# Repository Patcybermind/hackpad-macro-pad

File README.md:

# Pat's macropad
this was made for [highway](https://highway.hackclub.com) 
like some of the other projects on my github

## Features
- 8 keys
- oled display
- multiple modes / key presets

## PCB
Here are pictures of my pcb:

| **Schematic** | **PCB** |
|---------------|---------|
|||

[x] I ran DRC and there are 0 errors

## CAD

top and bottom are joined with m3 screws and heat inserts

## Firmware

The display tells you what mode you are in and in can be cycled with one of the keys

## BOM
- 1 SEEEDUINO XIAO RP2040
- 8x hackpad switches
- 8x hackpad keycaps
- 1x hackpad oled display
- 2x hackpad neopixels
- 4x M3x16mm screws
- 4x M3x5mx4mm heatset inserts

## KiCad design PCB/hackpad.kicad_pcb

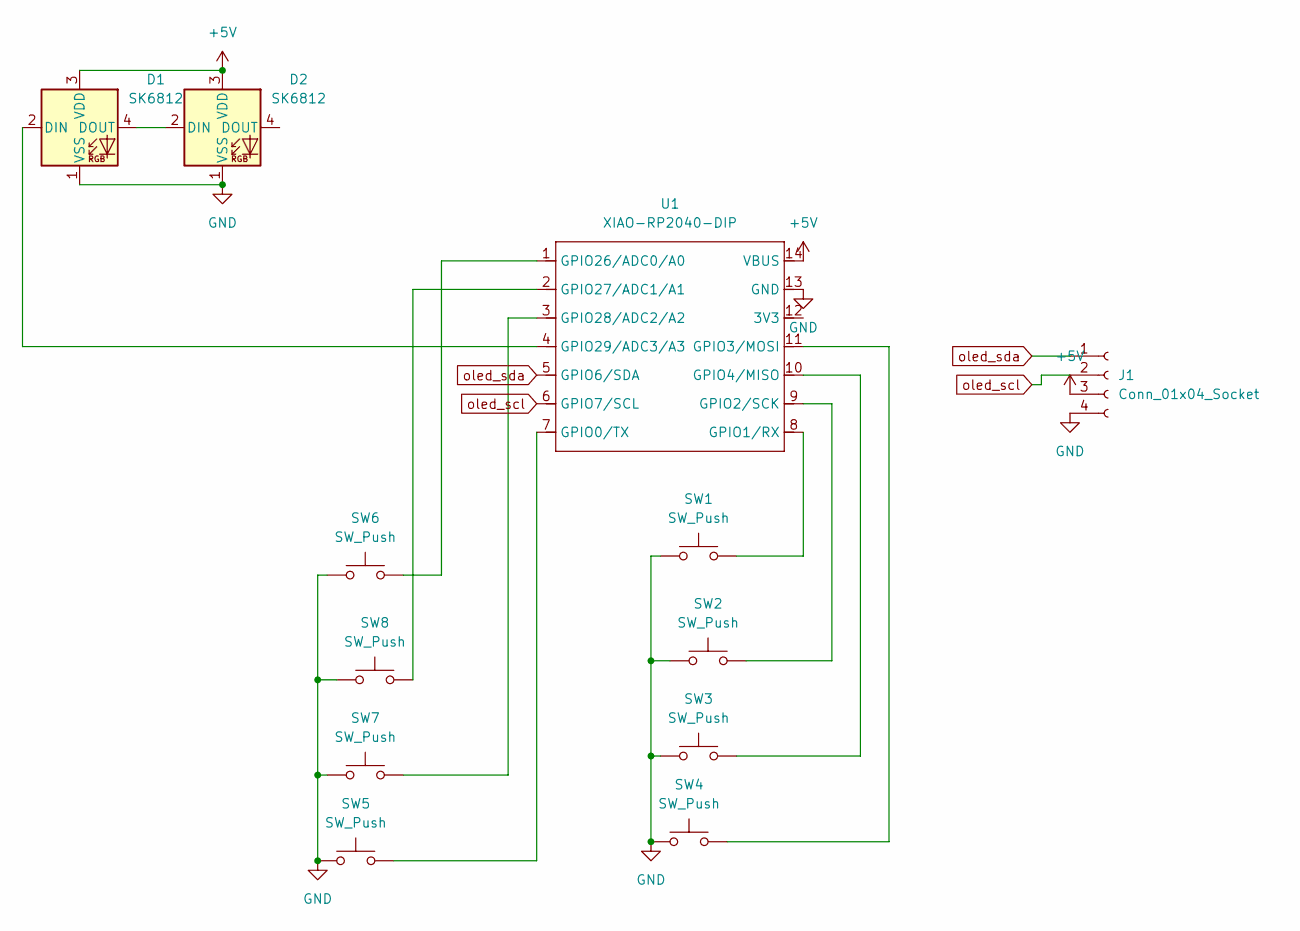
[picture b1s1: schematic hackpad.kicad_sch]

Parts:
D1, D2: SK6812; LED_SK6812_PLCC4_5.0x5.0mm_P3.2mm
J1: Conn_01x04_Socket; PinHeader_1x04_P2.54mm_Vertical
SW1, SW2, SW3, SW4, SW5, SW6, SW7, SW8: SW_Push; SW_Cherry_MX_1.00u_PCB
U1: XIAO-RP2040-DIP

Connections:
+5V: D1.3 (VDD), D2.3 (VDD), J1.3, U1.14 (VBUS)
GND: D1.1 (VSS), D2.1 (VSS), J1.4, SW1.1, SW2.1, SW3.1, SW4.1, SW5.1, SW6.1, SW7.1, SW8.1, U1.13 (GND)
unnamed: D1.2 (DIN), U1.4 (GPIO29/ADC3/A3)
unnamed: D1.4 (DOUT), D2.2 (DIN)
unnamed: SW5.2, U1.7 (GPIO0/TX)
unnamed: SW1.2, U1.8 (GPIO1/RX)
unnamed: SW2.2, U1.9 (GPIO2/SCK)
unnamed: SW4.2, U1.11 (GPIO3/MOSI)
unnamed: SW3.2, U1.10 (GPIO4/MISO)
unnamed: SW6.2, U1.1 (GPIO26/ADC0/A0)
unnamed: SW8.2, U1.2 (GPIO27/ADC1/A1)
unnamed: SW7.2, U1.3 (GPIO28/ADC2/A2)
oled_scl: J1.2, U1.6 (GPIO7/SCL)
oled_sda: J1.1, U1.5 (GPIO6/SDA)

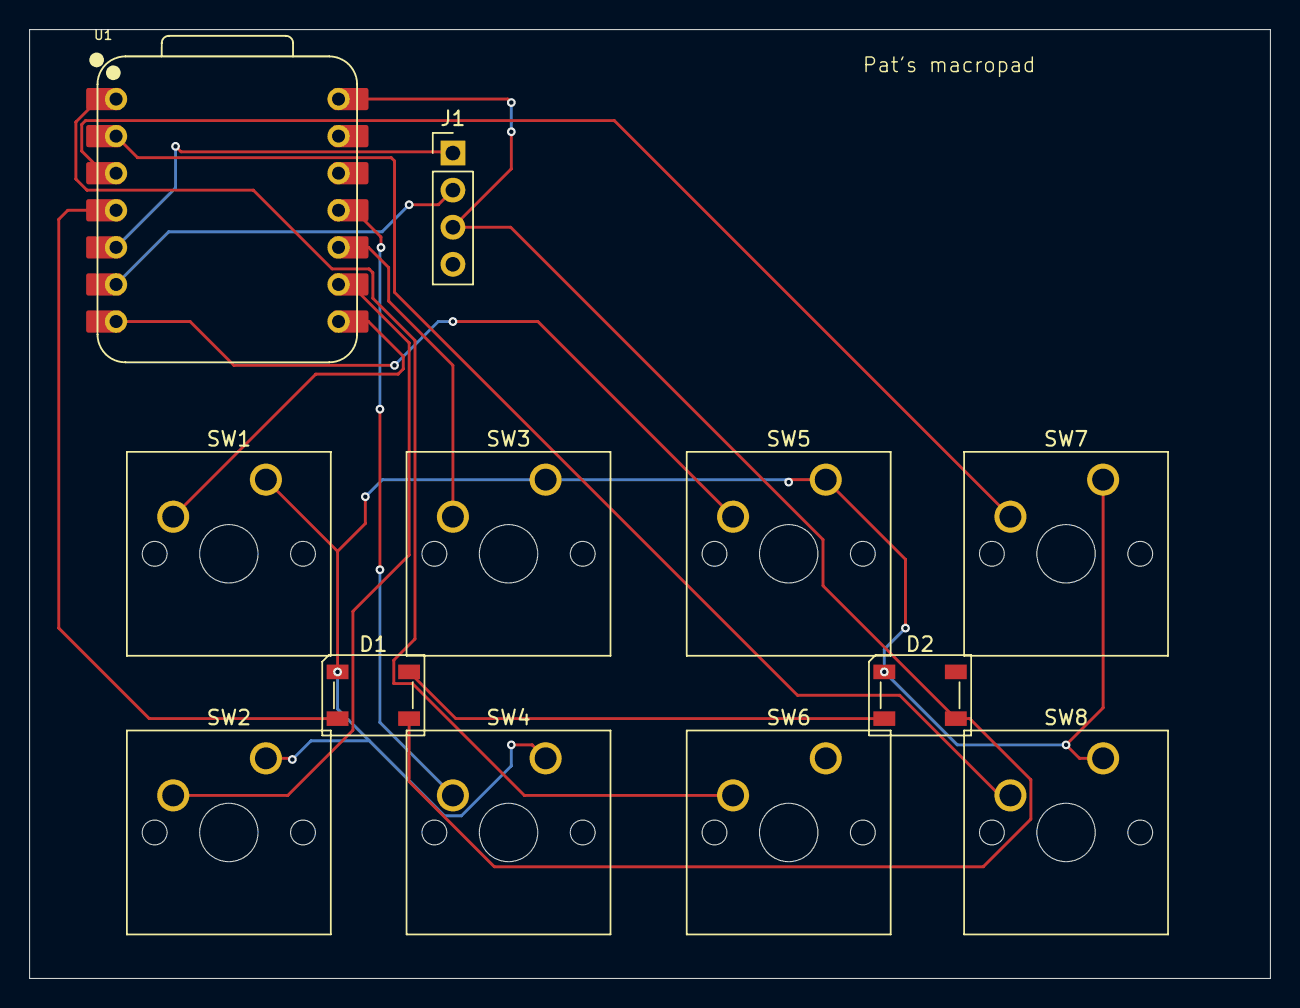
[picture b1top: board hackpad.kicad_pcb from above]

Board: 2 copper layers, 85.0 x 65.0 mm, 12 parts (0 on the bottom side), 14 nets.

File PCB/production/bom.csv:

Designator,Footprint,Quantity,Value,LCSC Part #
"D1, D2",LED_SK6812_PLCC4_5.0x5.0mm_P3.2mm,2,SK6812,
J1,PinHeader_1x04_P2.54mm_Vertical,1,Conn_01x04_Socket,
"SW1, SW2, SW3, SW4, SW5, SW6, SW7, SW8",SW_Cherry_MX_1.00u_PCB,8,SW_Push,
U1,XIAO-RP2040-DIP,1,XIAO-RP2040-DIP,

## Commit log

2025-06-27 added all kicad files
2025-06-29 done
2025-07-01 added production folder
2025-07-01 renamed to gerber
